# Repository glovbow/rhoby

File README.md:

# rhoby
source files for companion beam robot

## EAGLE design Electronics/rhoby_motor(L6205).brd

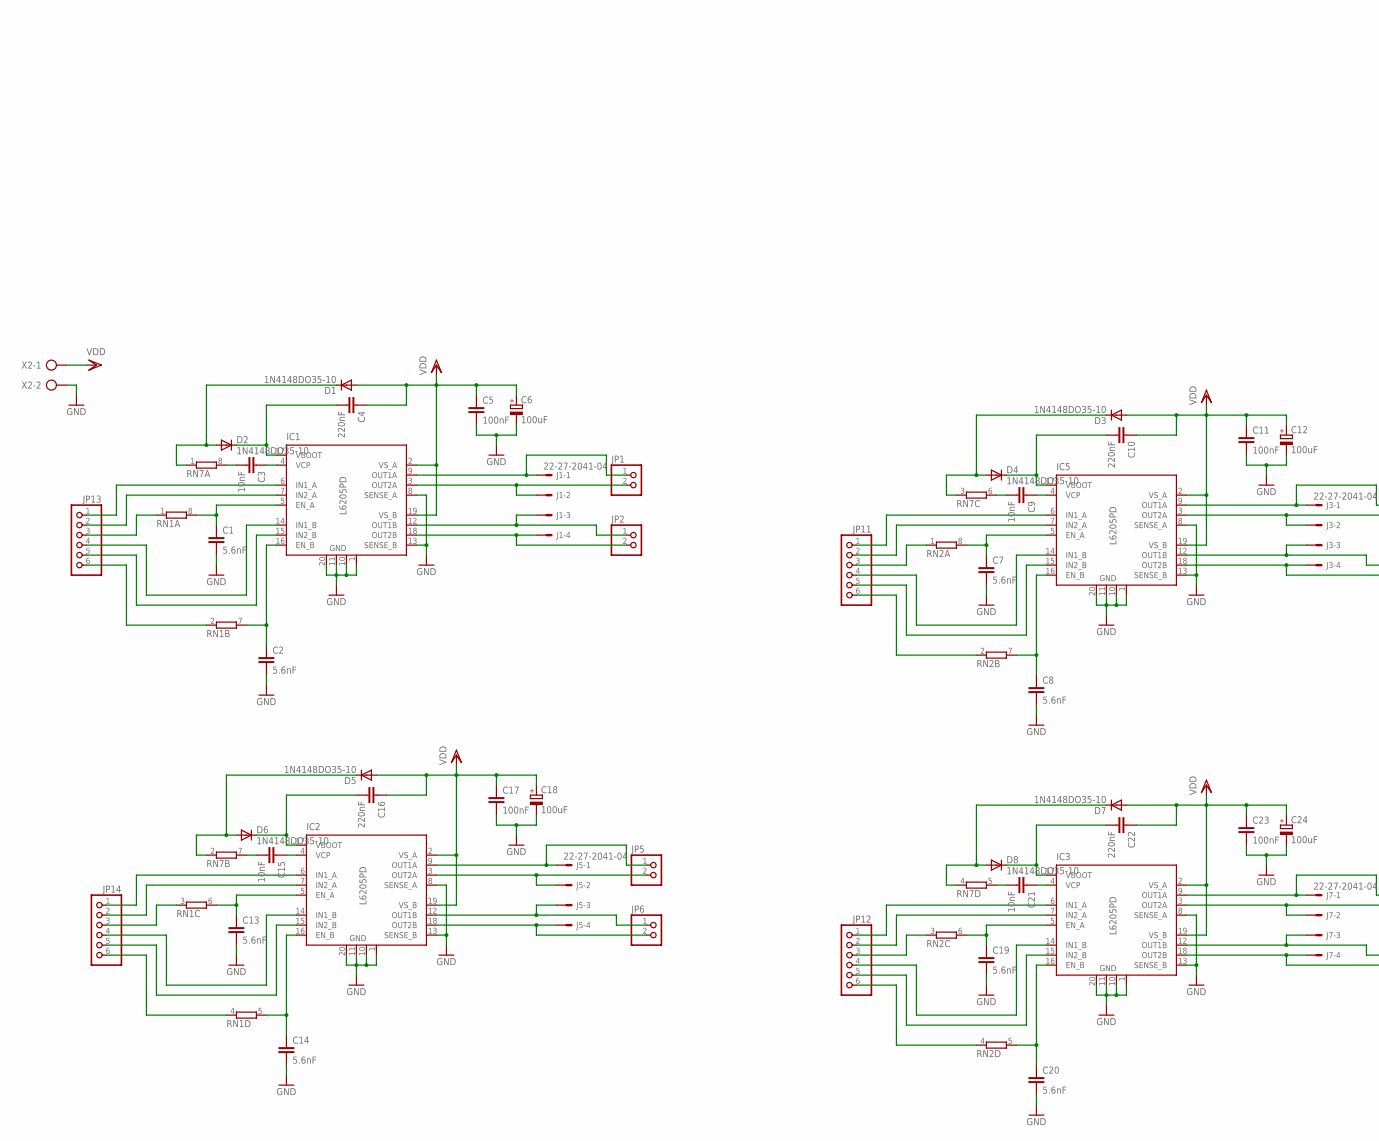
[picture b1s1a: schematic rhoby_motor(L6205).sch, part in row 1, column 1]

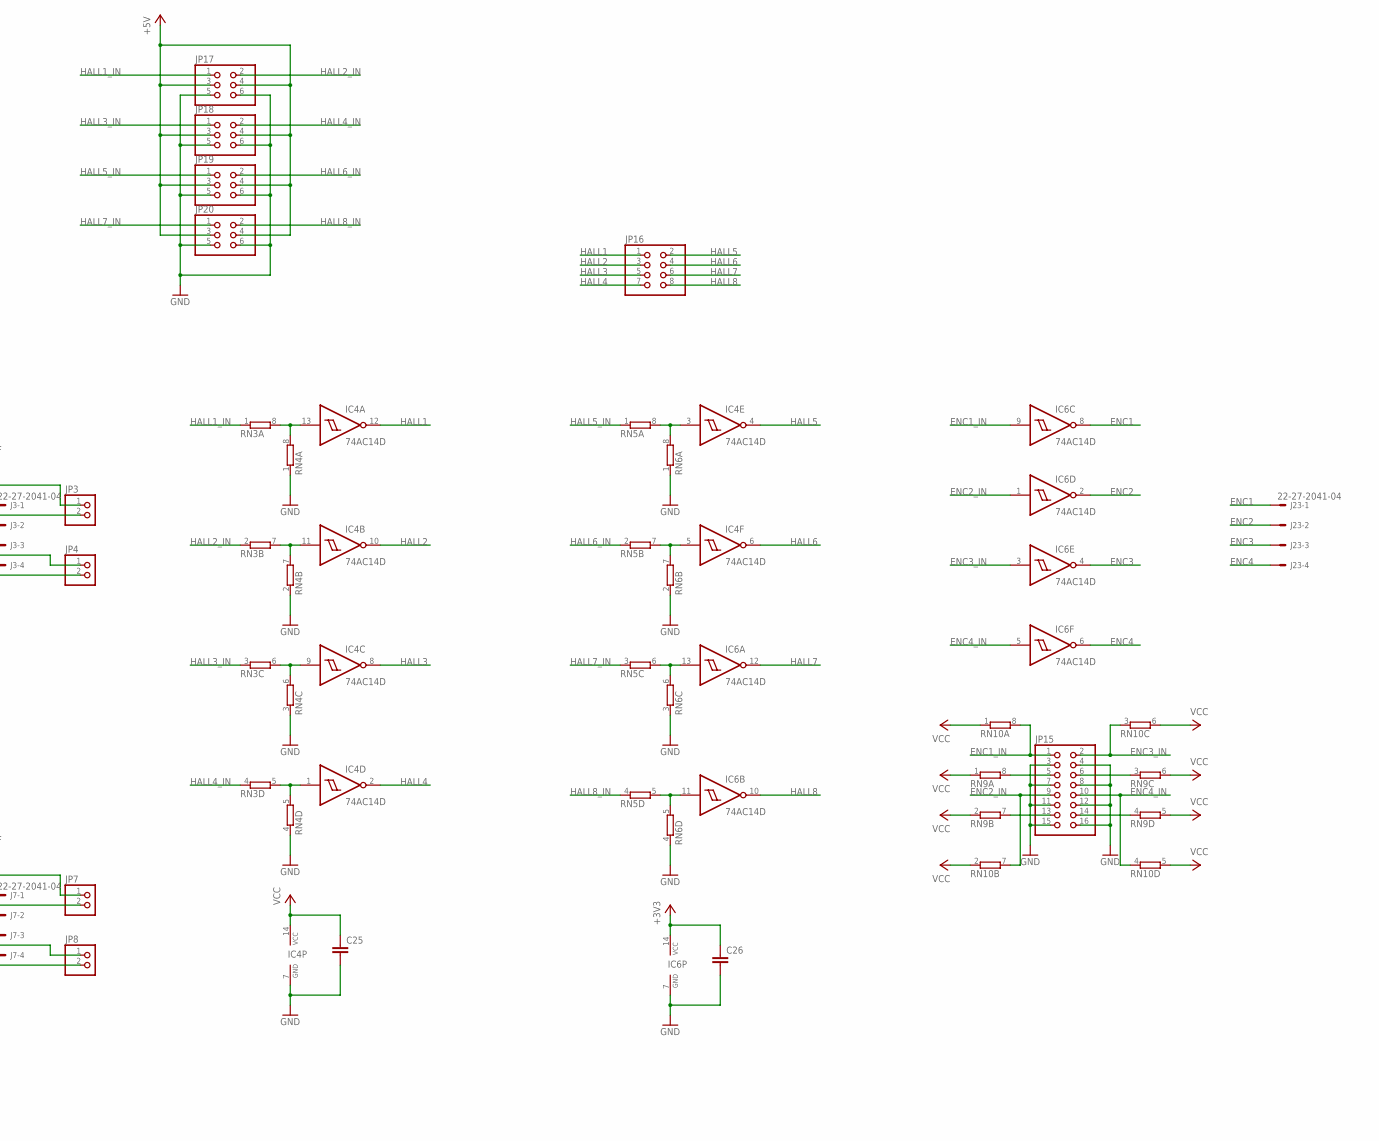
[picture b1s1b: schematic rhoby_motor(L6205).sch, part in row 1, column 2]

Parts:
C1, C2, C7, C8, C13, C14, C19, C20: 5.6nF; C0603K
C3, C9, C15, C21: 10nF; C0805K
C4, C10, C16, C22: 220nF; C0805K
C5, C11, C17, C23: 100nF; C2220K
C6, C12, C18, C24: 100uF; SMC_D
C25, C26: C-EUC0603K; C0603K
D1, D2, D3, D4, D5, D6, D7, D8: 1N4148DO35-10; DO35-10
IC1, IC2, IC3, IC5: L6205PD; POWERSO-20
IC4, IC6: 74AC14D; SO14
J1, J3, J5, J7, J23: 22-27-2041-04; 6410-04
JP1, JP2, JP3, JP4, JP5, JP6, JP7, JP8: PINHD-1X2; 1X02
JP11, JP12, JP13, JP14: PINHD-1X6; 1X06
JP15: PINHD-2X8; 2X08
JP16: PINHD-2X4; 2X04
JP17, JP18, JP19, JP20: PINHD-2X3; 2X03
RN1, RN2, RN3, RN4, RN5, RN6, RN7, RN9, RN10: 4R-NEXB38V; EXB38V
X2: AK500/2

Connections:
+3V3: C26.1, IC6.14 (VCC)
+5V: JP17.3, JP17.4, JP18.3, JP18.4, JP19.3, JP19.4, JP20.3, JP20.4
ENC1: IC6.8 (O), J23.1
ENC1_IN: IC6.9 (I), JP15.1, RN10.8 (2)
ENC2: IC6.2 (O), J23.2
ENC2_IN: IC6.1 (I), JP15.9, RN10.7 (2)
ENC3: IC6.4 (O), J23.3
ENC3_IN: IC6.3 (I), JP15.2, RN10.3 (1)
ENC4: IC6.6 (O), J23.4
ENC4_IN: IC6.5 (I), JP15.10, RN10.4 (1)
GND: C1.2, C2.2, C5.2, C6.-, C7.2, C8.2, C11.2, C12.-, C13.2, C14.2, C17.2, C18.-, C19.2, C20.2, C23.2, C24.-, C25.2, C26.2, IC1.1 (GND), IC1.8 (SENSE_A), IC1.10 (GND), IC1.11 (GND), IC1.13 (SENSE_B), IC1.20 (GND), IC2.1 (GND), IC2.8 (SENSE_A), IC2.10 (GND), IC2.11 (GND), IC2.13 (SENSE_B), IC2.20 (GND), IC3.1 (GND), IC3.8 (SENSE_A), IC3.10 (GND), IC3.11 (GND), IC3.13 (SENSE_B), IC3.20 (GND), IC4.7 (GND), IC5.1 (GND), IC5.8 (SENSE_A), IC5.10 (GND), IC5.11 (GND), IC5.13 (SENSE_B), IC5.20 (GND), IC6.7 (GND), JP15.3, JP15.4, JP15.7, JP15.8, JP15.11, JP15.12, JP15.15, JP15.16, JP17.5, JP17.6, JP18.5, JP18.6, JP19.5, JP19.6, JP20.5, JP20.6, RN4.1, RN4.2 (1), RN4.3 (1), RN4.4 (1), RN6.1, RN6.2 (1), RN6.3 (1), RN6.4 (1), X2.2
HALL1: IC4.12 (O), JP16.1
HALL1_IN: JP17.1, RN3.1
HALL2: IC4.10 (O), JP16.3
HALL2_IN: JP17.2, RN3.2 (1)
HALL3: IC4.8 (O), JP16.5
HALL3_IN: JP18.1, RN3.3 (1)
HALL4: IC4.2 (O), JP16.7
HALL4_IN: JP18.2, RN3.4 (1)
HALL5: IC4.4 (O), JP16.2
HALL5_IN: JP19.1, RN5.1
HALL6: IC4.6 (O), JP16.4
HALL6_IN: JP19.2, RN5.2 (1)
HALL7: IC6.12 (O), JP16.6
HALL7_IN: JP20.1, RN5.3 (1)
HALL8: IC6.10 (O), JP16.8
HALL8_IN: JP20.2, RN5.4 (1)
unnamed: IC1.6 (IN1_A), JP13.1
unnamed: IC1.7 (IN2_A), JP13.2
unnamed: C1.1, IC1.5 (EN_A), RN1.8 (2)
unnamed: IC1.14 (IN1_B), JP13.4
unnamed: D1.C, D2.A, RN7.1
unnamed: C2.1, IC1.16 (EN_B), RN1.7 (2)
unnamed: IC1.15 (IN2_B), JP13.5
unnamed: C3.1, IC1.4 (VCP)
unnamed: IC1.9 (OUT1A), J1.1, JP1.1
unnamed: IC1.3 (OUT2A), J1.2, JP1.2
unnamed: IC1.12 (OUT1B), J1.3, JP2.1
unnamed: IC1.18 (OUT2B), J1.4, JP2.2
unnamed: C4.2, D2.C, IC1.17 (VBOOT)
unnamed: C3.2, RN7.8 (2)
unnamed: JP13.6, RN1.2 (1)
unnamed: JP13.3, RN1.1
unnamed: C14.1, IC2.16 (EN_B), RN1.5 (2)
unnamed: IC2.9 (OUT1A), J5.1, JP5.1
unnamed: IC2.3 (OUT2A), J5.2, JP5.2
unnamed: C8.1, IC5.16 (EN_B), RN2.7 (2)
unnamed: IC5.9 (OUT1A), J3.1, JP3.1
unnamed: IC5.3 (OUT2A), J3.2, JP3.2
unnamed: IC5.12 (OUT1B), J3.3, JP4.1
unnamed: IC5.18 (OUT2B), J3.4, JP4.2
unnamed: C10.2, D4.C, IC5.17 (VBOOT)
unnamed: D3.C, D4.A, RN7.3 (1)
unnamed: C9.1, IC5.4 (VCP)
unnamed: C9.2, RN7.6 (2)
unnamed: IC5.6 (IN1_A), JP11.1
unnamed: IC5.7 (IN2_A), JP11.2
unnamed: C7.1, IC5.5 (EN_A), RN2.8 (2)
unnamed: IC5.14 (IN1_B), JP11.4
unnamed: IC5.15 (IN2_B), JP11.5
unnamed: JP11.6, RN2.2 (1)
unnamed: JP11.3, RN2.1
unnamed: IC2.12 (OUT1B), J5.3, JP6.1
unnamed: IC2.18 (OUT2B), J5.4, JP6.2
unnamed: C16.2, D6.C, IC2.17 (VBOOT)
unnamed: D5.C, D6.A, RN7.2 (1)
unnamed: C15.1, IC2.4 (VCP)
unnamed: C15.2, RN7.7 (2)
unnamed: IC2.6 (IN1_A), JP14.1
unnamed: IC2.7 (IN2_A), JP14.2
unnamed: C13.1, IC2.5 (EN_A), RN1.6 (2)
unnamed: IC2.14 (IN1_B), JP14.4
unnamed: IC2.15 (IN2_B), JP14.5
unnamed: JP14.6, RN1.4 (1)
unnamed: JP14.3, RN1.3 (1)
unnamed: C20.1, IC3.16 (EN_B), RN2.5 (2)
unnamed: IC3.9 (OUT1A), J7.1, JP7.1
unnamed: IC3.3 (OUT2A), J7.2, JP7.2
unnamed: IC3.12 (OUT1B), J7.3, JP8.1
unnamed: IC3.18 (OUT2B), J7.4, JP8.2
unnamed: C22.2, D8.C, IC3.17 (VBOOT)
unnamed: D7.C, D8.A, RN7.4 (1)
unnamed: C21.1, IC3.4 (VCP)
unnamed: C21.2, RN7.5 (2)
unnamed: IC3.6 (IN1_A), JP12.1
unnamed: IC3.7 (IN2_A), JP12.2
unnamed: C19.1, IC3.5 (EN_A), RN2.6 (2)
unnamed: IC3.14 (IN1_B), JP12.4
unnamed: IC3.15 (IN2_B), JP12.5
unnamed: JP12.6, RN2.4 (1)
unnamed: JP12.3, RN2.3 (1)
unnamed: IC4.13 (I), RN3.8 (2), RN4.8 (2)
unnamed: IC4.11 (I), RN3.7 (2), RN4.7 (2)
unnamed: IC4.9 (I), RN3.6 (2), RN4.6 (2)
unnamed: IC6.13 (I), RN5.6 (2), RN6.6 (2)
unnamed: IC4.5 (I), RN5.7 (2), RN6.7 (2)
unnamed: IC4.1 (I), RN3.5 (2), RN4.5 (2)
unnamed: IC6.11 (I), RN5.5 (2), RN6.5 (2)
unnamed: IC4.3 (I), RN5.8 (2), RN6.8 (2)
unnamed: JP15.13, RN9.7 (2)
unnamed: JP15.5, RN9.8 (2)
unnamed: JP15.6, RN9.3 (1)
unnamed: JP15.14, RN9.4 (1)
VCC: C25.1, IC4.14 (VCC), RN9.1, RN9.2 (1), RN9.5 (2), RN9.6 (2), RN10.1, RN10.2 (1), RN10.5 (2), RN10.6 (2)
VDD: C4.1, C5.1, C6.+, C10.1, C11.1, C12.+, C16.1, C17.1, C18.+, C22.1, C23.1, C24.+, D1.A, D3.A, D5.A, D7.A, IC1.2 (VS_A), IC1.19 (VS_B), IC2.2 (VS_A), IC2.19 (VS_B), IC3.2 (VS_A), IC3.19 (VS_B), IC5.2 (VS_A), IC5.19 (VS_B), X2.1

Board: 2 copper layers, 73 parts (33 on the bottom side), 105 nets, no tracks yet.

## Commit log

2018-03-04 Base for motor mounting
2018-03-24 add directory for version 1.0 electronics
    Schematic for motors driver almost done. Now I have only one issue: How
    make universal connection for optical encoders.
2018-06-04 New version of the motor board based on L6205 IC
2018-08-11 Changed some connectors
2018-08-12 Moved some components on bottom
